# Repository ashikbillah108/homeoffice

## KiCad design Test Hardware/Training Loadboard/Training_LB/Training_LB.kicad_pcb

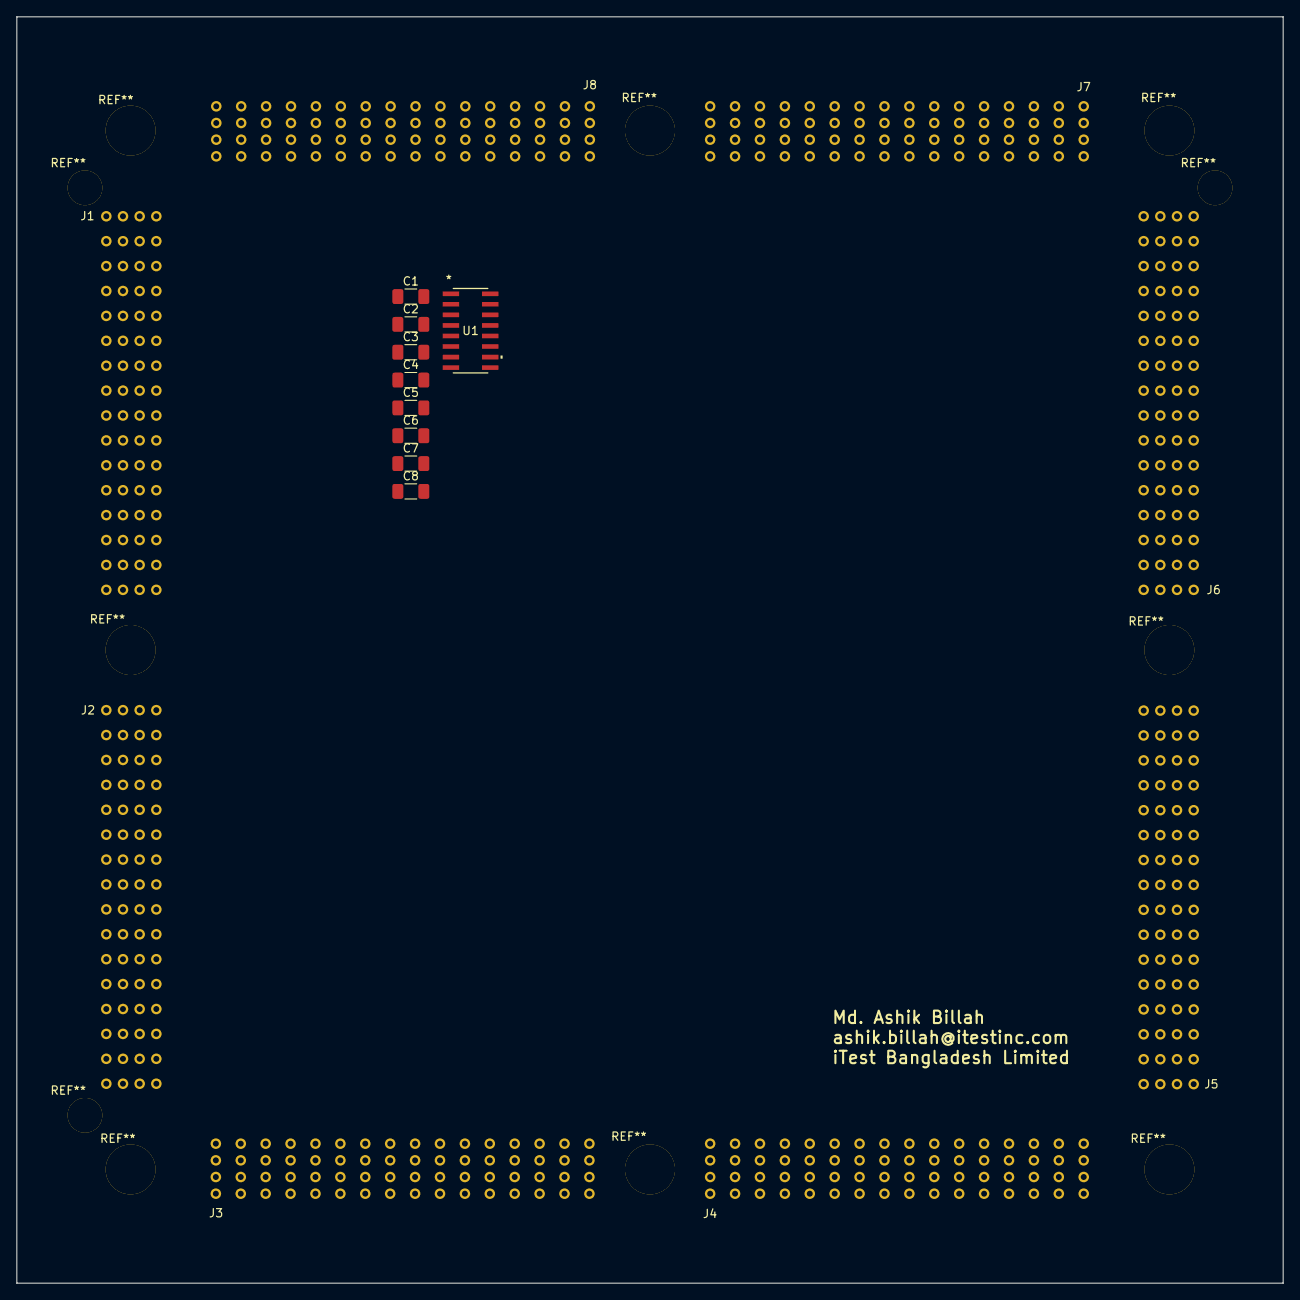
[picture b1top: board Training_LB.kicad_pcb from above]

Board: 4 copper layers, 152.4 x 152.4 mm, 17 parts (0 on the bottom side), 5 nets, no tracks yet.

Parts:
C1, C3, C5, C7: 0.1uF; C_1206_3216Metric_Pad1.33x1.80mm_HandSolder
C2, C4, C6, C8: 10uF; C_1206_3216Metric_Pad1.33x1.80mm_HandSolder
J1, J2, J3, J4, J5, J6, J7, J8: DUT64
U1: MCP3008; SOIC16-N_MC_MCH

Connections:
GND: C1.2, C2.2, C3.2, C4.2, C5.2, C6.2, C7.2, C8.2, J1.G1, J1.G2, J1.G3, J1.G4, J1.G5, J1.G6, J1.G7, J1.G8, J1.G9, J1.G10, J1.G11, J1.G12, J1.G13, J1.G14, J1.G15, J1.G16, J1.G17, J1.G18, J1.G19, J1.G20, J1.G21, J1.G22, J1.G23, J1.G24, J1.G25, J1.G26, J1.G27, J1.G28, J1.G29, J1.G30, J1.G31, J1.G32, J2.G1, J2.G2, J2.G3, J2.G4, J2.G5, J2.G6, J2.G7, J2.G8, J2.G9, J2.G10, J2.G11, J2.G12, J2.G13, J2.G14, J2.G15, J2.G16, J2.G17, J2.G18, J2.G19, J2.G20, J2.G21, J2.G22, J2.G23, J2.G24, J2.G25, J2.G26, J2.G27, J2.G28, J2.G29, J2.G30, J2.G31, J2.G32, J3.G1, J3.G2, J3.G3, J3.G4, J3.G5, J3.G6, J3.G7, J3.G8, J3.G9, J3.G10, J3.G11, J3.G12, J3.G13, J3.G14, J3.G15, J3.G16, J3.G17, J3.G18, J3.G19, J3.G20, J3.G21, J3.G22, J3.G23, J3.G24, J3.G25, J3.G26, J3.G27, J3.G28, J3.G29, J3.G30, J3.G31, J3.G32, J4.G1, J4.G2, J4.G3, J4.G4, J4.G5, J4.G6, J4.G7, J4.G8, J4.G9, J4.G10, J4.G11, J4.G12, J4.G13, J4.G14, J4.G15, J4.G16, J4.G17, J4.G18, J4.G19, J4.G20, J4.G21, J4.G22, J4.G23, J4.G24, J4.G25, J4.G26, J4.G27, J4.G28, J4.G29, J4.G30, J4.G31, J4.G32, J5.G1, J5.G2, J5.G3, J5.G4, J5.G5, J5.G6, J5.G7, J5.G8, J5.G9, J5.G10, J5.G11, J5.G12, J5.G13, J5.G14, J5.G15, J5.G16, J5.G17, J5.G18, J5.G19, J5.G20, J5.G21, J5.G22, J5.G23, J5.G24, J5.G25, J5.G26, J5.G27, J5.G28, J5.G29, J5.G30, J5.G31, J5.G32, J6.G1, J6.G2, J6.G3, J6.G4, J6.G5, J6.G6, J6.G7, J6.G8, J6.G9, J6.G10, J6.G11, J6.G12, J6.G13, J6.G14, J6.G15, J6.G16, J6.G17, J6.G18, J6.G19, J6.G20, J6.G21, J6.G22, J6.G23, J6.G24, J6.G25, J6.G26, J6.G27, J6.G28, J6.G29, J6.G30, J6.G31, J6.G32, J7.G1, J7.G2, J7.G3, J7.G4, J7.G5, J7.G6, J7.G7, J7.G8, J7.G9, J7.G10, J7.G11, J7.G12, J7.G13, J7.G14, J7.G15, J7.G16, J7.G17, J7.G18, J7.G19, J7.G20, J7.G21, J7.G22, J7.G23, J7.G24, J7.G25, J7.G26, J7.G27, J7.G28, J7.G29, J7.G30, J7.G31, J7.G32, J8.G1, J8.G2, J8.G3, J8.G4, J8.G5, J8.G6, J8.G7, J8.G8, J8.G9, J8.G10, J8.G11, J8.G12, J8.G13, J8.G14, J8.G15, J8.G16, J8.G17, J8.G18, J8.G19, J8.G20, J8.G21, J8.G22, J8.G23, J8.G24, J8.G25, J8.G26, J8.G27, J8.G28, J8.G29, J8.G30, J8.G31, J8.G32, U1.9 (DGND), U1.14 (AGND)
Vdd_MCP3008: C1.1, C2.1, U1.16 (Vdd)
Vdd_MCP4901: C5.1, C6.1
Vref_MCP3008: C3.1, C4.1, U1.15 (Vref)
Vref_MCP4901: C7.1, C8.1

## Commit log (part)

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2026-04-24 New Project PCB
2026-04-27 Project Completed
2026-04-29 GRIFFI Upload
2026-05-04 farihaapu file
2026-05-09 10052026
